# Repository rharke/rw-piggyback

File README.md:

# RamWorks Piggyback²

This card provides a way to use a modern Apple IIe RAM card (such as the GW4203B from Garret's Workshop) with a RamWorks-style RGB piggyback card.

For the RGB piggyback, it is compatible with classic piggyback cards like the Applied Engineering RGB Card, Digital Prism, and Color Link, as well as the a2heaven VGA piggyback card.

For the RAM, the GW4203B is recommended, but you could also use one of the older GW 2MB cards, or one of the "small" Apple 80-column cards. (But why?) It just needs to be 2" tall or less.

You can optionally install a USB port and/or a 2-pin header to allow a convenient way to tap 5V power for other peripherals, such as a WiModem232.

A 220pF capacitor (exact value probably doesn't matter much) may be installed (and is recommended). This provides some filtering on the FRCTXT line, which is involved in flipping between DHGR modes. Without it, it has been reported that sometimes an attached Digital Prism will erroneously flip from DHGR mono back into DHGR color at random intervals. Not all cards/computers seem to demonstrate this issue, but the capacitor shouldn't hurt anything.

## Shop

I sell these cards in my [shop](http://lexingtoninfosystems.com).

Since this project is MIT licensed, please feel free to build your own if you like! Note however that the 60-pin edge connectors often have to be purchased in bulk.

## Photos

## Bill of Materials

* 60-pin 0.1" pin / 0.2" row right-angle female edge connector (suggested: [EDAC 	
395-060-558-201](https://www.digikey.com/en/products/detail/edac-inc/395-060-558-201/10885109))
* 24-pin 0.1" female header (suggested: [Sullins PPPC241LFBN-RC](https://www.digikey.com/en/products/detail/sullins-connector-solutions/PPPC241LFBN-RC/810196))
* 8-pin 0.1" female header (suggested: [Sullins PPPC081LFBN-RC](https://www.digikey.com/product-detail/en/sullins-connector-solutions/PPPC081LFBN-RC/S7041-ND/810180))
* 2x 0.5" rubber bumper (suggested: [3M Bumpon SJ6512](https://www.digikey.com/en/products/detail/3m/SJ6512/3866123))
* Optional: USB-A female receptacle (suggested: [Stewart SS-52100-001](https://www.digikey.com/en/products/detail/stewart-connector/SS-52100-001/7902377))
* Optional: 2-pin 0.1" right angle male header (suggested: [Sullins PRPC002SBAN-M71RC](https://www.digikey.com/en/products/detail/sullins-connector-solutions/PRPC002SBAN-M71RC/2775332))
* Optional: 220pF 0.2" ceramic capacitor (suggested: [KEMET C322C221K1G5TA](https://www.digikey.com/en/products/detail/kemet/C322C221K1G5TA/3726159))

## Assembly

You can use the gerbers in `rw-piggyback-gerber.zip` to have the PCB manufactured at the FAB of your choice.

* Insert and solder the 8-pin and the 24-pin female headers to the BACK of the PCB. You MUST do this first, before you solder in the edge connector.
* Cut off pin 47 from the edge connector, as close to the plastic as you can. You can tell which pin is 47 by holding the connector up to the PCB. It is the one in the position that crosses over with the 24-pin female header. You won't be able to insert the connector into the PCB until you cut the pin, because the 24-pin female header is occupying that position.
* Please 2 rubber bumpers in the circles indicated on the FRONT of the PCB.
* Insert the 60-pin edge connector into the FRONT of the PCB, using the rubber bumpers to ensure proper spacing from the PCB. Try to keep it straight, and solder it in place.
* Trim the excess length off of the edge connector leads on the back of the PCB, if necessary. Not all brands of edge connectors will have excess length (but the EDAC ones do).
* Solder in the USB receptable, the 2-pin header, and the capacitor to the FRONT of the PCB.

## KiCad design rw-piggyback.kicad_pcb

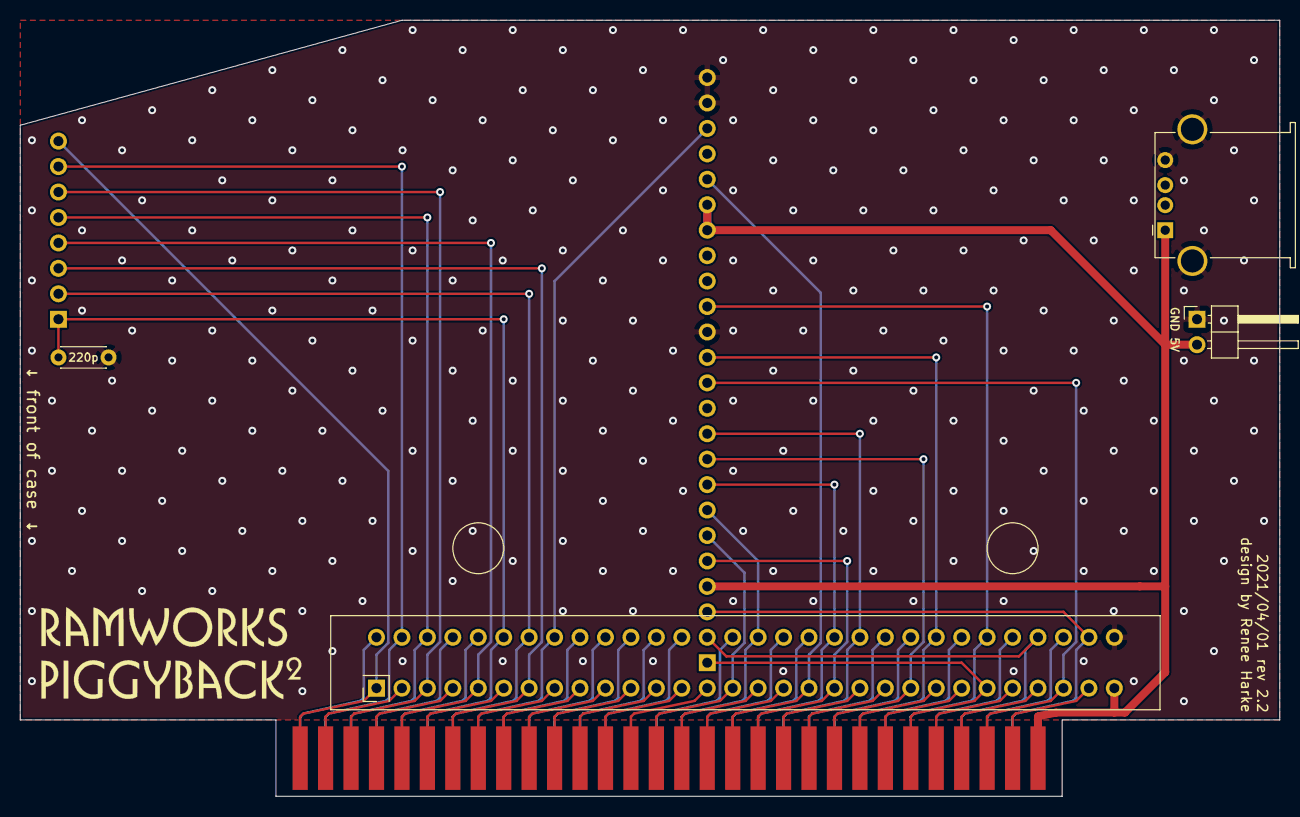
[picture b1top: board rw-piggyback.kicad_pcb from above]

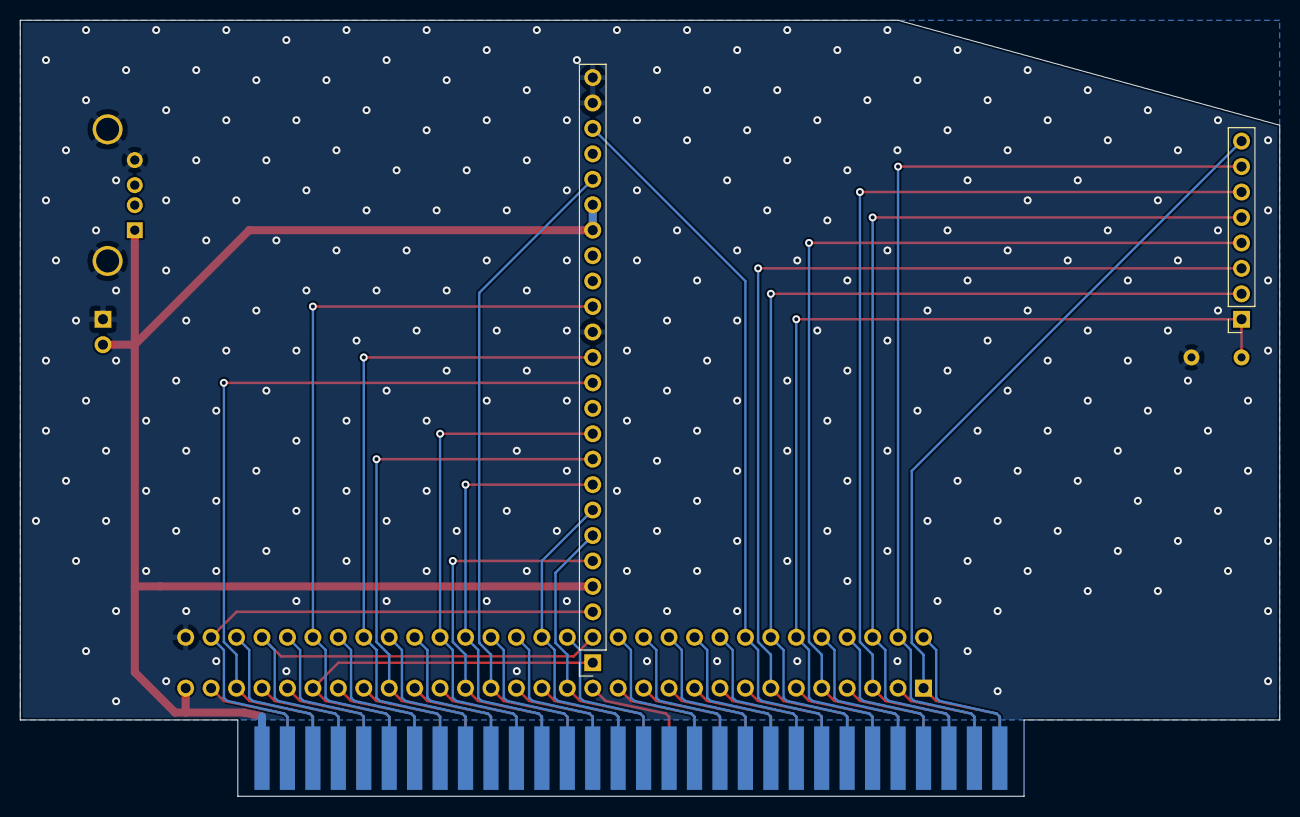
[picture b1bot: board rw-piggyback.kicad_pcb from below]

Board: 2 copper layers, 125.7 x 77.5 mm, 8 parts (2 on the bottom side), 59 nets.

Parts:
C1: 220p; C_Disc_D4.3mm_W1.9mm_P5.00mm
G1: RamWorks_Piggyback^2_Logo; piggyback-logo-2
J1: Logic Board; AppleIIeAux
J2: RAM Card; CardEdge_EDAC_3x5-060_2x30_P2.54mm_CCW_No47
J3: Piggyback A; PinSocket_1x08_P2.54mm_Vertical
J4: Piggyback B; PinSocket_1x24_P2.54mm_Vertical
J5: Power; PinHeader_1x02_P2.54mm_Horizontal
J6: USB A; USB_A_Stewart_SS-52100-001_Horizontal

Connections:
+5V: J1.30, J2.30, J4.4, J4.18, J4.19, J5.2, J6.1
/3M58: J1.1, J2.1, J3.8
/7M: J1.59, J2.59, J3.7
/14M: J1.32, J2.32, J4.3
/80VID: J1.25, J2.25, J4.1
/ALTVID: J1.27, J2.27
/AN3: J1.50, J2.50
/C07X: J1.6, J2.6
/CASEN: J1.37, J2.37
/CLRGAT: J1.24, J2.24
/EN80: J1.26, J2.26
/ENTMG: J1.60, J2.60
/ENVID: J1.29, J2.29
/FRCTXT: C1.2, J1.55, J2.55, J3.1
/GR: J1.58, J2.58, J3.5
/LDPS: J1.34, J2.34, J4.2
/MD0: J1.44, J2.44
/MD1: J1.43, J2.43
/MD2: J1.40, J2.40
/MD3: J1.39, J2.39
/MD4: J1.21, J2.21
/MD5: J1.20, J2.20
/MD6: J1.17, J2.17
/MD7: J1.16, J2.16
/PCAS: J1.33, J2.33
/PHI0: J1.23, J2.23
/PHI1: J1.36, J2.36, J4.15
/PRAS: J1.4, J2.4
/Q3: J1.53, J2.53, J4.22
/RA0: J1.51, J2.51
/RA1: J1.10, J2.10
/RA2: J1.49, J2.49
/RA3: J1.48, J2.48
/RA4: J1.13, J2.13
/RA5: J1.14, J2.14
/RA6: J1.46, J2.46
/RA7: J1.9, J2.9
/RA9: J1.56, J2.56
/RA10: J1.57, J2.57
/ROMEN1: J1.11, J2.11
/ROMEN2: J1.12, J2.12
/RW: J1.52, J2.52
/RW80: J1.35, J2.35
/SEGA: J1.8, J2.8
/SEGB: J1.54, J2.54, J3.2
/SEROUT: J1.28, J2.28, J4.12
/SYNC: J1.3, J2.3, J3.6
/VC: J1.5, J2.5, J3.4
/VID0: J1.45, J2.45, J4.7
/VID1: J1.42, J2.42, J4.8
/VID2: J1.41, J2.41, J4.10
/VID3: J1.38, J2.38, J4.13
/VID4: J1.22, J2.22, J4.9
/VID5: J1.19, J2.19, J4.5
/VID6: J1.18, J2.18, J4.20
/VID7: J1.15, J2.15, J4.6
/VID7M: J1.2, J2.2
/WNDW: J1.7, J2.7, J3.3
GND: C1.1, J1.31, J2.31, J4.14, J4.23, J4.24, J5.1, J6.4, J6.5

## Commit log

2021-05-16 Initial
2021-05-16 Repoint
2021-05-17 Gerbers, license, readme, etc.
2021-05-17 Add another photo
2021-05-17 Typo
2021-05-17 Add missing instruction
